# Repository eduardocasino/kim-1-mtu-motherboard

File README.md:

# KIM-1 Motherboard for MTU Cards

## **WARNING**

**ALTHOUGH THE CARDS HAVE BEEN TESTED NOW, THERE MAY BE MORE ERRORS. USE AT YOUR OWN RISK!!!**

If you ordered the first revision PCB, please see the "Rev. 1 Fix" section below.

If you ordered earlier revisions of the aux cards (RS-232 and USB), please see the "Aux. Cards Fix" section below. 

## **UPDATE**

There is now a third auxiliary card option, for connecting the KIM-1 terminal wirelessly using an ESP8266. This new board is not affected by the problems referred above.

This card requires to transfer its firmware to the ESP8266. [Please, see the set up instructions here](https://github.com/eduardocasino/kim-1-mtu-motherboard/blob/main/kim-1-aux-card-esp/README.md)

## About

Welcome to my KIM-1 Motherboardfor MTU cards repository.

This board follows the MTU standard for the KIM-1 expansion and application buses and enables to connect up to five cards, like the [K-1008](https://github.com/eduardocasino/k-1008-visable-memory-card-replica). All the CPU lines are buffered. Additionally, all signals of the KIM-1 ports are replicated on corresponding edge connectors to allow further expansions.

Two audio jacks allow for cassette deck connection and two optional daughterboards provide IEC and RS-232 or USB serial connections, and also a connector compatible with Corsham's SD Shield.

The MTU bus connects 1 to 1 to the KIM-1 expansion connector with the exception of pins 2,3, 16, 17, 18, 19, 20 and X, because MTU boards use some of these pins for power and expanded 18 bit address bus (See page 33 of the [MTU Fall 1980 6502 Peripherals and Software catalog](hhttp://retro.hansotten.nl/6502-sbc/mtu/) Lines 19 and 20 are connected to pins J (K7) and K (DECODE ENABLE) of the KIM-1 application connector, respectively. Those two signals can be limited to just the first or the first and second connectors by opening some jumpers.

A five screw terminal block provides power connections for both the KIM-1 (GND, +5V and +12V regulated) and the expansion boards (+7.5V and +16V unregulated). 

Detail of the two auxiliary boards:

This is how an example setup with one K-1008 board and a [RAM/ROM expansion card](https://github.com/eduardocasino/kim-1-mtu-ram-rom) would look like:

**NOTE**: [This expansion board is a much simpler option](https://github.com/eduardocasino/kim-1-mtu-expansion-card) if you just need to connect some MTU cards. Those are engineered so they put less than 1 TTL load on the CPU buses, so no buffering is really needed. Why the buffering, then? Well, just for fun.

## Licensing

This is a personal project that I am sharing in case it is of interest to any retrocomputing enthusiast and all the information in this repository is provided "as is", without warranty of any kind. I am not liable for any damages that may occur, whether it be to individuals, objects, KIM-1 computers, kittens or any other pets.

This work is licensed under a [Creative Commons Attribution-ShareAlike 4.0 International License](http://creativecommons.org/licenses/by-sa/4.0/).

See the LICENSE.md file for details.

## Rev. 1 Fix

If you tried to build revision 1 of this board, you found out that it does not work (See [Issue #2](https://github.com/eduardocasino/kim-1-mtu-motherboard/issues/2))

You can [install this simple PCB](https://github.com/eduardocasino/kim-1-mtu-motherboard/rev-1-fix) or, alternatively, perform this bodge on the back of the PCB:

Using a cutter, carefully cut these two spokes at pin 19 of U4:

Grab a 14 pin IC socket with flat pins. Bend pins 1,2,3,7 and 14 outwards and cut the rest.

Solder wires to the pins as per this image:

Cover the back of the socket with non conductive tape. Attach the wires to these spots on the motherboard:

Place a 74LS00 in the socket (check the orientation!) and fix evrything to the PCB using some tape, like in this image. I took K7 from another pin, but it is all the same:

## Aux. Cards Fix

If you tried to build earlier revisions of the auxiliary boards (both RS-232 and USB), you may have found out that they do not work with Corsham's SD Shield, although they work fine with IEC disks (See [Issue #3](https://github.com/eduardocasino/kim-1-mtu-motherboard/issues/3))

If you need them to work with the SD Shield, you can perform this simple fix. **WARNING: Doing so, the cards will no longer work with IEC disks**

The fix is the same for both cards. Using a cutter, carefully cut these two tracks:

## Changelog
#### 17/02/2024
* Release Rev. 3 (fixes the auxiliary cards, the motherboard is unchanged)
* IEC socket footprint also supports Commodore-style sockets
* Add instructions to fix original auxiliary boards so they work with IEC disks.

#### 21/01/2024
* Release Rev. 2
* Add instructions to fix Rev. 1 boards.

#### 03/01/2024
* Minor silkscreen update

#### 02/01/2024
* Disable data bus transceiver when DECEN or K7 are active (low)

## Acknowledgements

* Hans Otten and his [Retro Computing blog](http://retro.hansotten.nl/). Documentation of MTU's line of hardware expansions for the KIM-1

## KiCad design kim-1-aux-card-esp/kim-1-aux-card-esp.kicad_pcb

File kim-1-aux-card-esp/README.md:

## Wireless terminal board

This design is based on a setup by Ryan Roth, mentioned in this [Google Groups thread](https://groups.google.com/g/pal6502/c/w8N0uSgJXQY), and the ESP8266 needs to be [programmed with his firmware](https://github.com/ryaneroth/ESP8266-SerialTelnet). For convenience, I keep a [copy of his repo here](https://github.com/eduardocasino/ESP8266-SerialTelnet).

## Firmware install instructions

1. Download and install the latest **Arduino IDE 2.X (preferred) or 1.6.X** from [https://www.arduino.cc/en/Main/Software](https://www.arduino.cc/en/Main/Software)

2. Install **ESP8266** Arduino support using Boards Manager: [https://github.com/esp8266/Arduino#installing-with-boards-manager](https://github.com/esp8266/Arduino#installing-with-boards-manager)

    ***Only*** for IDE 1.6.X, force install version >= 2.4.0. Replace package URL with: [https://github.com/esp8266/Arduino/releases/download/2.4.0-rc1/package_esp8266com_index.json](https://github.com/esp8266/Arduino/releases/download/2.4.0-rc1/package_esp8266com_index.json)

3. Install Install the following libraries:
    * WifiManager: [https://github.com/tzapu/WiFiManager#install-through-library-manager](https://github.com/tzapu/WiFiManager#install-through-library-manager)

4. Put the three bridges in the "**FLASH**" position and connect the board to your computer using an USB to serial adapter.

5. Select board `Generic ESP8266Module`

6. Upload the Sketch contained in `telnetserver` folder from the [ESP8266-SerialTelnet](https://github.com/eduardocasino/ESP8266-SerialTelnet) repo.

7. The moment the `Connecting...` message appears in the console, press the "**RESET**" button and, while holding it", press momentarily the "**FLASH**" button. Then, release the "**RESET**" button. Wait until the sketch is uploaded.

8. Connect to the ESP8266 WiFi network and go to "http://192.168.4.1". Configure connection to your AP, set password, then switch back to your local wifi

9. Disconnect the card and put the bridges back to the "**RUN**" position. Now, you can install it into the motherboard.

10. Connect to the ESP8266 using a Telnet client. Set local echo to off.

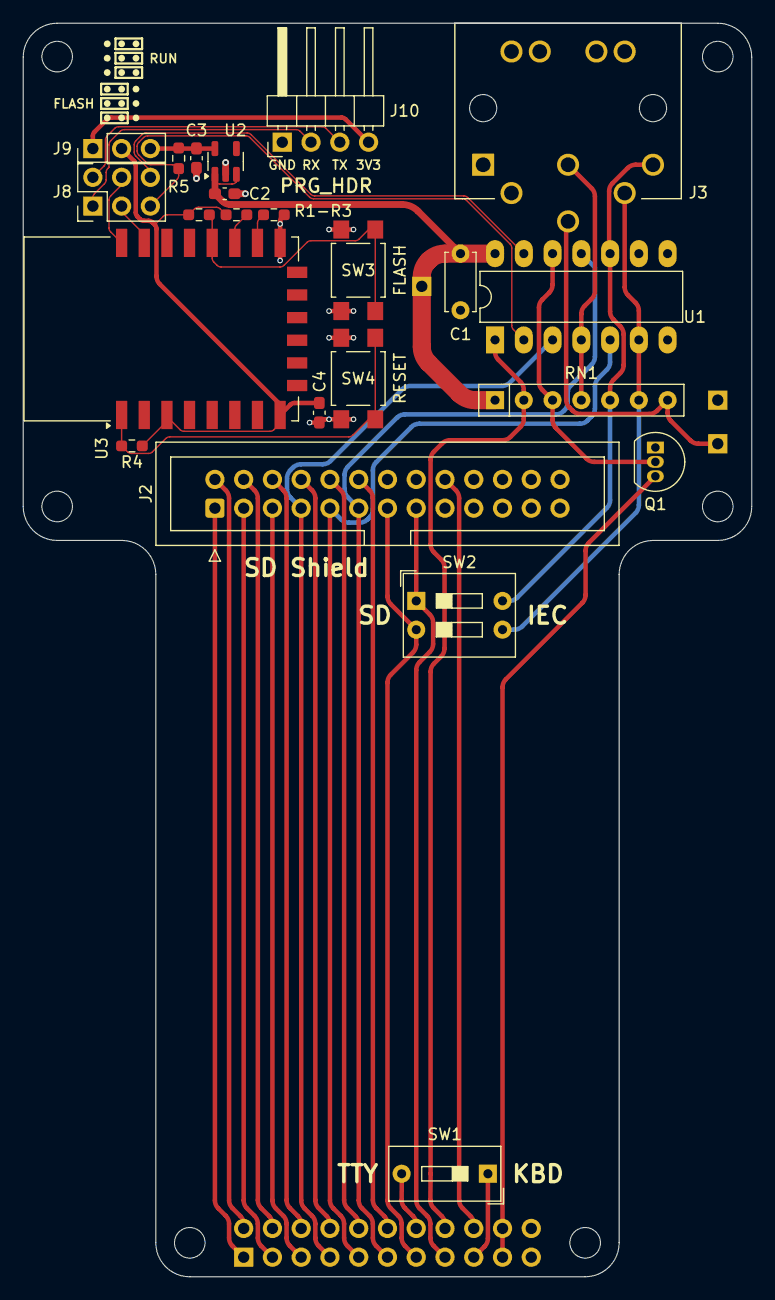
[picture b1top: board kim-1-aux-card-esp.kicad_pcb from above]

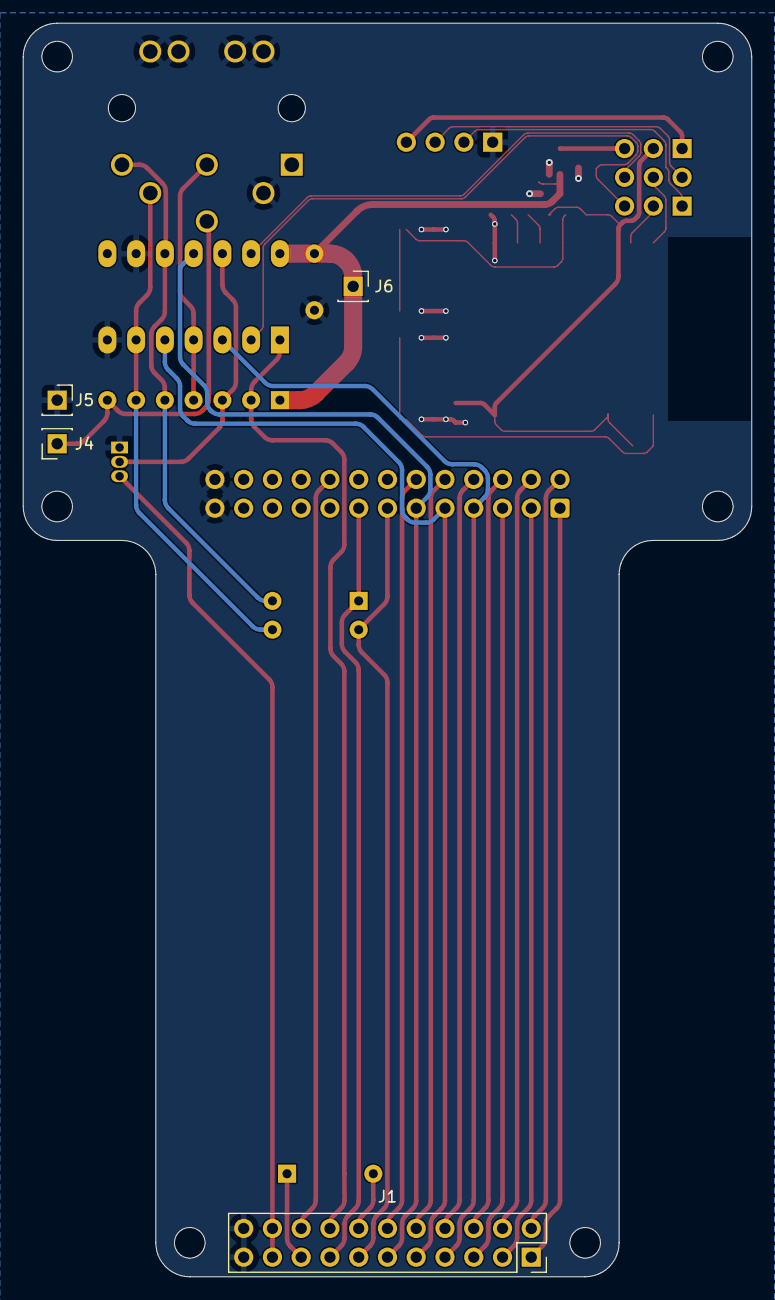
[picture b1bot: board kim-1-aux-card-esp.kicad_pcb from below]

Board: 2 copper layers, 64.3 x 110.7 mm, 27 parts (4 on the bottom side), 39 nets.

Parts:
C1: 100nF; C_Disc_D5.0mm_W2.5mm_P5.00mm
C2, C3: 1uF; C_0603_1608Metric_Pad1.08x0.95mm_HandSolder
C4: 100nF; C_0603_1608Metric_Pad1.08x0.95mm_HandSolder
J1: Motherboard; PinSocket_2x11_P2.54mm_Vertical
J2: SD_Shield; IDC-Header_2x13_P2.54mm_Vertical
J3: DIN-6; CUI_SDS-60J
J4: Reset; PinSocket_1x01_P2.54mm_Vertical
J5: GND; PinSocket_1x01_P2.54mm_Vertical
J6: +5V; PinSocket_1x01_P2.54mm_Vertical
J8: RUN_FLASH; PinHeader_2x03_P2.54mm_Vertical
J9: RUN_FLASH; PinHeader_1x03_P2.54mm_Vertical
J10: PRG_HDR; PinHeader_1x04_P2.54mm_Horizontal
Q1: PN2222A; TO-92_Inline
R1, R2, R3, R4, R5: 10K; R_0603_1608Metric_Pad0.98x0.95mm_HandSolder
RN1: 3K3; R_Array_SIP7
SW1: TTY_KBD; SW_DIP_SPSTx01_Slide_9.78x4.72mm_W7.62mm_P2.54mm
SW2: SD_IEC; SW_DIP_SPSTx02_Slide_9.78x7.26mm_W7.62mm_P2.54mm
SW3: FLASH; SW_SPST_TL3305A
SW4: RESET; SW_SPST_TL3305A
U1: 74LS06; DIP-14_W7.62mm_LongPads
U2: TPS7A0233DBVR; SOT-23-5
U3: ESP-12F; ESP-12E

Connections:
+3V3: C3.1, J9.3, R5.1, U2.5 (OUT)
+5V: C1.1, C2.1, J6.1, RN1.1 (R1), U1.14 (VCC), U2.1 (IN), U2.3 (EN)
/COLA: J1.14, SW1.2
/KBD: J1.19, J1.20, Q1.3 (C)
/PA0: J1.1, J2.1
/PA1: J1.3, J2.3
/PA2: J1.5, J2.5
/PA3: J1.7, J2.7, U1.3
/PA4: J1.9, J2.9, U1.5
/PA5: J1.11, J2.11, U1.11
/PA6: J1.13, J2.13, SW2.2
/PA7: J1.15, J2.15, SW2.1
/PB0: J1.2, J2.2
/PB1: J1.4, J2.4
/PB2: J1.6, J2.6
/PB3: J1.8, J2.8
/PB4: J1.10, J2.10
/PB5: J1.12, J2.12
/PB7: J1.18, J2.18
/PTR: J1.16, RN1.2 (R1.2), U1.1
/ROW3: J1.17, SW1.1
GND: C1.2, C2.2, C3.2, C4.1, J1.21, J1.22, J2.25, J2.26, J3.2, J3.E1, J3.E2, J5.1, J10.1, Q1.1 (E), R3.2, SW3.1 (A), SW4.1 (A), U1.7 (GND), U1.9, U2.2 (GND), U3.15 (GND)
unnamed: J3.6, J4.1, RN1.7 (R6.2)
unnamed: J8.3, U3.21 (GPIO3/RXD)
unnamed: J8.4, U3.22 (GPIO1/TXD)
unnamed: J8.5, R5.2, U1.2
unnamed: J8.6, U1.13
unnamed: C4.2, J9.2, R1.1, R2.1, R4.1, U3.3 (EN), U3.8 (VCC)
unnamed: J8.1, J10.2
unnamed: J8.2, J10.3
unnamed: J9.1, J10.4
unnamed: Q1.2 (B), RN1.3 (R2.2), U1.12
unnamed: J3.3, RN1.4 (R3.2), U1.4
unnamed: J3.5, RN1.5 (R4.2), SW2.4, U1.10
unnamed: J3.4, RN1.6 (R5.2), SW2.3, U1.6
unnamed: R1.2, SW3.2 (B), U3.18 (GPIO0)
unnamed: R4.2, SW4.2 (B), U3.1 (~RST)
unnamed: R2.2, U3.17 (GPIO2)
unnamed: R3.1, U3.16 (GPIO15)

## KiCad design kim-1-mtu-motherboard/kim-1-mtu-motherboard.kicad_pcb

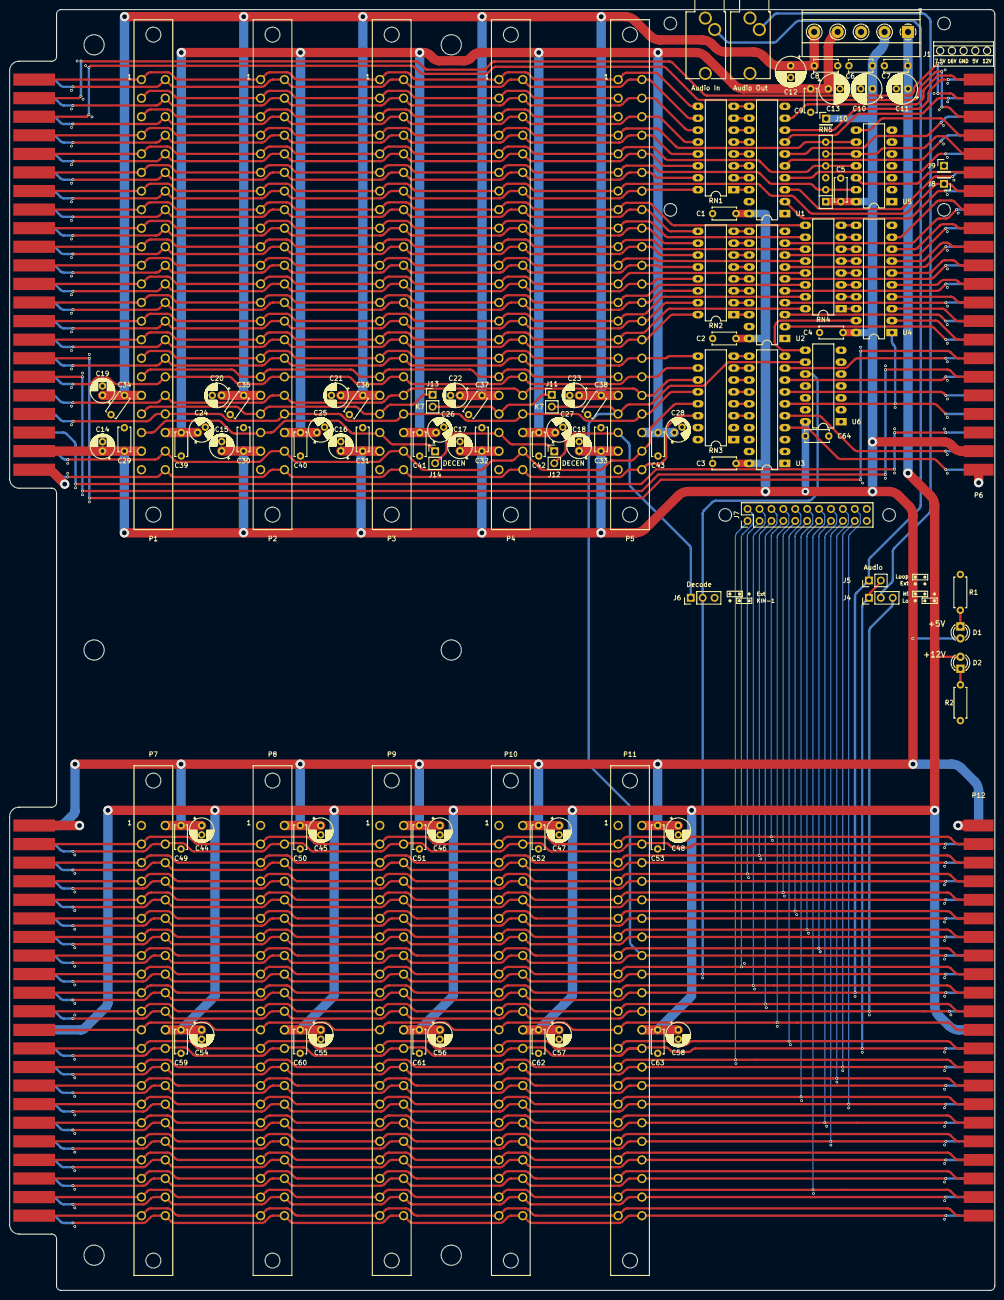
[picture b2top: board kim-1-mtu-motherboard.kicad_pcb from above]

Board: 2 copper layers, 210.0 x 273.0 mm, 107 parts (0 on the bottom side), 161 nets.

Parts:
C1, C2, C3, C4, C5, C6, C7, C8, C9, C29, C30, C31, C32, C33, C34, C35, C36, C37, C38, C39, C40, C41, C42, C43, C49, C50, C51, C52, C53, C59, C60, C61, C62, C63, C64: 100nF; C_Disc_D5.0mm_W2.5mm_P5.00mm
C10, C11, C12, C13: 100uF; CP_Radial_D6.3mm_P2.50mm
C14, C15, C16, C17, C18, C19, C20, C21, C22, C23, C24, C25, C26, C27, C28, C44, C45, C46, C47, C48, C54, C55, C56, C57, C58: 47uF; CP_Radial_D5.0mm_P2.00mm
D1: RED; LED_D3.0mm
D2: YELLOW; LED_D3.0mm
J1: Power_Connector; TerminalBlock_Phoenix_MKDS-1,5-5_1x05_P5.00mm_Horizontal
J2: Audio Out; Jack_3.5mm_35RAPC2AVN4_Horizontal_CircularHoles
J3: Audio In; Jack_3.5mm_35RAPC2AVN4_Horizontal_CircularHoles
J4: Audio HI/LO; PinHeader_1x03_P2.54mm_Vertical
J5: Audio Loop; PinHeader_1x02_P2.54mm_Vertical
J6: Decode; PinHeader_1x03_P2.54mm_Vertical
J7: Daughterboard; PinHeader_2x11_P2.54mm_Vertical
J8: RESET; PinHeader_1x01_P2.54mm_Vertical
J9, J10: GND; PinHeader_1x01_P2.54mm_Vertical
J11, J13: K7; PinHeader_1x02_P2.54mm_Vertical
J12, J14: DECEN; PinHeader_1x02_P2.54mm_Vertical
P1, P2, P3, P4, P5, P7, P8, P9, P10, P11: EXP_BOARD; EDAC-3.96-2x22
P6, P12: KIM-1; KIM_EDGE
P13: KIM_EXP; KIM_CONN
P14: KIM_APPL; KIM_CONN
R1: 330R; R_Axial_DIN0207_L6.3mm_D2.5mm_P7.62mm_Horizontal
R2: 1K; R_Axial_DIN0207_L6.3mm_D2.5mm_P7.62mm_Horizontal
RN1, RN2, RN3, RN4: 33R; DIP-16_W7.62mm_LongPads
RN5: 3K3; R_Array_SIP6
U1, U2, U3: 74HCT541; DIP-20_W7.62mm_LongPads
U4: 74LS245; DIP-20_W7.62mm_LongPads
U5: 74LS07; DIP-14_W7.62mm_LongPads
U6: 74LS00; DIP-14_W7.62mm_LongPads

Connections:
+5V: C1.1, C2.1, C3.1, C4.1, C5.1, C6.2, C10.1, C14.1, C15.1, C16.1, C17.1, C18.1, C29.1, C30.1, C31.1, C32.1, C33.1, C44.1, C45.1, C46.1, C47.1, C48.1, C49.1, C50.1, C51.1, C52.1, C53.1, C64.1, D1.2 (A), J1.2, J10.1, P1.21 (+5V), P2.21 (+5V), P3.21 (+5V), P4.21 (+5V), P5.21 (+5V), P6.21 (+5V), P7.A (+5V), P8.A (+5V), P9.A (+5V), P10.A (+5V), P11.A (+5V), P12.A (+5V), P13.21 (+5V), P14.A (+5V), RN5.1 (common), U1.20 (VCC), U2.20 (VCC), U3.20 (VCC), U4.20 (VCC), U5.14 (VCC), U6.14 (VCC)
+7.5V_RAW: C8.2, C12.1, C19.1, C20.1, C21.1, C22.1, C23.1, C34.1, C35.1, C36.1, C37.1, C38.1, J1.5, P1.18 (+7.5V_RAW), P2.18 (+7.5V_RAW), P3.18 (+7.5V_RAW), P4.18 (+7.5V_RAW), P5.18 (+7.5V_RAW)
+12V: C7.2, C11.1, C54.1, C55.1, C56.1, C57.1, C58.1, C59.1, C60.1, C61.1, C62.1, C63.1, D2.2 (A), J1.1, P7.N (+12V), P8.N (+12V), P9.N (+12V), P10.N (+12V), P11.N (+12V), P12.N (+12V), P14.N (+12V)
+16V_RAW: C9.2, C13.1, C24.1, C25.1, C26.1, C27.1, C28.1, C39.1, C40.1, C41.1, C42.1, C43.1, J1.4, P1.X (+16V_RAW), P2.X (+16V_RAW), P3.X (+16V_RAW), P4.X (+16V_RAW), P5.X (+16V_RAW)
/A0: P6.A (A0), U1.8 (A6)
/A1: P6.B (A1), U1.7 (A5)
/A2: P6.C (A2), U1.6 (A4)
/A3: P6.D (A3), U1.5 (A3)
/A4: P6.E (A4), U1.4 (A2)
/A5: P6.F (A5), U1.3 (A1)
/A6: P6.H (A6), U1.2 (A0)
/A7: P6.J (A7), U2.9 (A7)
/A8: P6.K (A8), U2.8 (A6)
/A9: P6.L (A9), U2.7 (A5)
/A10: P6.M (A10), U2.6 (A4)
/A11: P6.N (A11), U2.5 (A3)
/A12: P6.P (A12), U2.4 (A2)
/A13: P6.R (A13), U2.3 (A1)
/A14: P6.S (A14), U2.2 (A0)
/A15: P6.T (A15), U3.9 (A7)
/AUDIN: J3.T, J5.1, P7.L (AUDIN), P8.L (AUDIN), P9.L (AUDIN), P10.L (AUDIN), P11.L (AUDIN), P12.L (AUDIN), P14.L (AUDIN)
/AUD_H: J4.1, J5.2, P7.P (AUD_H), P8.P (AUD_H), P9.P (AUD_H), P10.P (AUD_H), P11.P (AUD_H), P12.P (AUD_H), P14.P (AUD_H)
/AUD_L: J4.3, P7.M (AUD_L), P8.M (AUD_L), P9.M (AUD_L), P10.M (AUD_L), P11.M (AUD_L), P12.M (AUD_L), P14.M (AUD_L)
/BA0: P1.A (A0), P2.A (A0), P3.A (A0), P4.A (A0), P5.A (A0), P13.A (A0), RN1.10 (R7.2)
/BA1: P1.B (A1), P2.B (A1), P3.B (A1), P4.B (A1), P5.B (A1), P13.B (A1), RN1.11 (R6.2)
/BA2: P1.C (A2), P2.C (A2), P3.C (A2), P4.C (A2), P5.C (A2), P13.C (A2), RN1.12 (R5.2)
/BA3: P1.D (A3), P2.D (A3), P3.D (A3), P4.D (A3), P5.D (A3), P13.D (A3), RN1.13 (R4.2)
/BA4: P1.E (A4), P2.E (A4), P3.E (A4), P4.E (A4), P5.E (A4), P13.E (A4), RN1.14 (R3.2)
/BA5: P1.F (A5), P2.F (A5), P3.F (A5), P4.F (A5), P5.F (A5), P13.F (A5), RN1.15 (R2.2)
/BA6: P1.H (A6), P2.H (A6), P3.H (A6), P4.H (A6), P5.H (A6), P13.H (A6), RN1.16 (R1.2)
/BA7: P1.J (A7), P2.J (A7), P3.J (A7), P4.J (A7), P5.J (A7), P13.J (A7), RN2.9 (R8.2)
/BA8: P1.K (A8), P2.K (A8), P3.K (A8), P4.K (A8), P5.K (A8), P13.K (A8), RN2.10 (R7.2)
/BA9: P1.L (A9), P2.L (A9), P3.L (A9), P4.L (A9), P5.L (A9), P13.L (A9), RN2.11 (R6.2)
/BA10: P1.M (A10), P2.M (A10), P3.M (A10), P4.M (A10), P5.M (A10), P13.M (A10), RN2.12 (R5.2)
/BA11: P1.N (A11), P2.N (A11), P3.N (A11), P4.N (A11), P5.N (A11), P13.N (A11), RN2.13 (R4.2)
/BA12: P1.P (A12), P2.P (A12), P3.P (A12), P4.P (A12), P5.P (A12), P13.P (A12), RN2.14 (R3.2)
/BA13: P1.R (A13), P2.R (A13), P3.R (A13), P4.R (A13), P5.R (A13), P13.R (A13), RN2.15 (R2.2)
/BA14: P1.S (A14), P2.S (A14), P3.S (A14), P4.S (A14), P5.S (A14), P13.S (A14), RN2.16 (R1.2)
/BA15: P1.T (A15), P2.T (A15), P3.T (A15), P4.T (A15), P5.T (A15), P13.T (A15), RN3.9 (R8.2)
/BD0: P1.15 (D0), P2.15 (D0), P3.15 (D0), P4.15 (D0), P5.15 (D0), P13.15 (D0), RN4.16 (R1.2)
/BD1: P1.14 (D1), P2.14 (D1), P3.14 (D1), P4.14 (D1), P5.14 (D1), P13.14 (D1), RN4.15 (R2.2)
/BD2: P1.13 (D2), P2.13 (D2), P3.13 (D2), P4.13 (D2), P5.13 (D2), P13.13 (D2), RN4.14 (R3.2)
/BD3: P1.12 (D3), P2.12 (D3), P3.12 (D3), P4.12 (D3), P5.12 (D3), P13.12 (D3), RN4.13 (R4.2)
/BD4: P1.11 (D4), P2.11 (D4), P3.11 (D4), P4.11 (D4), P5.11 (D4), P13.11 (D4), RN4.12 (R5.2)
/BD5: P1.10 (D5), P2.10 (D5), P3.10 (D5), P4.10 (D5), P5.10 (D5), P13.10 (D5), RN4.11 (R6.2)
/BD6: P1.9 (D6), P2.9 (D6), P3.9 (D6), P4.9 (D6), P5.9 (D6), P13.9 (D6), RN4.10 (R7.2)
/BD7: P1.8 (D7), P2.8 (D7), P3.8 (D7), P4.8 (D7), P5.8 (D7), P13.8 (D7), RN4.9 (R8.2)
/BDECEN: J14.1, P1.20 (~DECODE_ENABLE), P2.20 (~DECODE_ENABLE), P3.20 (~DECODE_ENABLE)
/BK7: J13.1, P1.19 (~VECTOR_FETCH), P2.19 (~VECTOR_FETCH), P3.19 (~VECTOR_FETCH)
/BRAMRW: P1.Z (RAMRW), P2.Z (RAMRW), P3.Z (RAMRW), P4.Z (RAMRW), P5.Z (RAMRW), P13.Z (RAMRW), RN3.14 (R3.2)
/BRO: P1.5 (R0), P2.5 (R0), P3.5 (R0), P4.5 (R0), P5.5 (R0), P13.5 (R0), RN5.4 (R3), U5.11
/BR/~W: P1.V (R/~W), P2.V (R/~W), P3.V (R/~W), P4.V (R/~W), P5.V (R/~W), P13.V (R/~W), RN3.11 (R6.2)
/BSYNC: P1.1 (SYNC), P2.1 (SYNC), P3.1 (SYNC), P4.1 (SYNC), P5.1 (SYNC), P13.1 (SYNC), RN1.9 (R8.2)
/B~R/W: P1.W (~R/W), P2.W (~R/W), P3.W (~R/W), P4.W (~R/W), P5.W (~R/W), P13.W (~R/W), RN3.12 (R5.2)
/B~Ø2: P1.Y (~Ø2), P2.Y (~Ø2), P3.Y (~Ø2), P4.Y (~Ø2), P5.Y (~Ø2), P13.Y (~Ø2), RN3.13 (R4.2)
/BØ2: P1.U (Ø2), P2.U (Ø2), P3.U (Ø2), P4.U (Ø2), P5.U (Ø2), P13.U (Ø2), RN3.10 (R7.2)
/COLA: J7.14, P7.21 (COLA), P8.21 (COLA), P9.21 (COLA), P10.21 (COLA), P11.21 (COLA), P12.21 (COLA), P14.21 (COLA)
/COLB: P7.19 (COLB), P8.19 (COLB), P9.19 (COLB), P10.19 (COLB), P11.19 (COLB), P12.19 (COLB), P14.19 (COLB)
/COLC: P7.Y (COLC), P8.Y (COLC), P9.Y (COLC), P10.Y (COLC), P11.Y (COLC), P12.Y (COLC), P14.Y (COLC)
/COLD: P7.22 (COLD), P8.22 (COLD), P9.22 (COLD), P10.22 (COLD), P11.22 (COLD), P12.22 (COLD), P14.22 (COLD)
/COLE: P7.20 (COLE), P8.20 (COLE), P9.20 (COLE), P10.20 (COLE), P11.20 (COLE), P12.20 (COLE), P14.20 (COLE)
/COLF: P7.18 (COLF), P8.18 (COLF), P9.18 (COLF), P10.18 (COLF), P11.18 (COLF), P12.18 (COLF), P14.18 (COLF)
/COLG: P7.W (COLG), P8.W (COLG), P9.W (COLG), P10.W (COLG), P11.W (COLG), P12.W (COLG), P14.W (COLG)
/D0: P6.15 (D0), U4.2 (A0)
/D1: P6.14 (D1), U4.3 (A1)
/D2: P6.13 (D2), U4.4 (A2)
/D3: P6.12 (D3), U4.5 (A3)
/D4: P6.11 (D4), U4.6 (A4)
/D5: P6.10 (D5), U4.7 (A5)
/D6: P6.9 (D6), U4.8 (A6)
/D7: P6.8 (D7), U4.9 (A7)
/DECEN: J6.2, P7.K (DECEN), P8.K (DECEN), P9.K (DECEN), P10.K (DECEN), P11.K (DECEN), P12.K (DECEN), P14.K (DECEN), U6.10
/K0: P7.B (K0), P8.B (K0), P9.B (K0), P10.B (K0), P11.B (K0), P12.B (K0), P14.B (K0)
/K1: P7.C (K1), P8.C (K1), P9.C (K1), P10.C (K1), P11.C (K1), P12.C (K1), P14.C (K1)
/K2: P7.D (K2), P8.D (K2), P9.D (K2), P10.D (K2), P11.D (K2), P12.D (K2), P14.D (K2)
/K3: P7.E (K3), P8.E (K3), P9.E (K3), P10.E (K3), P11.E (K3), P12.E (K3), P14.E (K3)
/K4: P7.F (K4), P8.F (K4), P9.F (K4), P10.F (K4), P11.F (K4), P12.F (K4), P14.F (K4)
/K5: P7.H (K5), P8.H (K5), P9.H (K5), P10.H (K5), P11.H (K5), P12.H (K5), P14.H (K5)
/K6: P6.16 (K6), P13.16 (K6)
/K7: J11.2, P5.19 (~VECTOR_FETCH), P7.J (K7), P8.J (K7), P9.J (K7), P10.J (K7), P11.J (K7), P12.J (K7), P14.J (K7), U6.9
/KBD: J7.20, P7.T (KBD), P8.T (KBD), P9.T (KBD), P10.T (KBD), P11.T (KBD), P12.T (KBD), P14.T (KBD)
/KBD_R: J7.19, P7.R (KBD_R), P8.R (KBD_R), P9.R (KBD_R), P10.R (KBD_R), P11.R (KBD_R), P12.R (KBD_R), P14.R (KBD_R)
/PA0: J7.1, P7.14 (PA0), P8.14 (PA0), P9.14 (PA0), P10.14 (PA0), P11.14 (PA0), P12.14 (PA0), P14.14 (PA0)
/PA1: J7.3, P7.4 (PA1), P8.4 (PA1), P9.4 (PA1), P10.4 (PA1), P11.4 (PA1), P12.4 (PA1), P14.4 (PA1)
/PA2: J7.5, P7.3 (PA2), P8.3 (PA2), P9.3 (PA2), P10.3 (PA2), P11.3 (PA2), P12.3 (PA2), P14.3 (PA2)
/PA3: J7.7, P7.2 (PA3), P8.2 (PA3), P9.2 (PA3), P10.2 (PA3), P11.2 (PA3), P12.2 (PA3), P14.2 (PA3)
/PA4: J7.9, P7.5 (PA4), P8.5 (PA4), P9.5 (PA4), P10.5 (PA4), P11.5 (PA4), P12.5 (PA4), P14.5 (PA4)
/PA5: J7.11, P7.6 (PA5), P8.6 (PA5), P9.6 (PA5), P10.6 (PA5), P11.6 (PA5), P12.6 (PA5), P14.6 (PA5)
/PA6: J7.13, P7.7 (PA6), P8.7 (PA6), P9.7 (PA6), P10.7 (PA6), P11.7 (PA6), P12.7 (PA6), P14.7 (PA6)
/PA7: J7.15, P7.8 (PA7), P8.8 (PA7), P9.8 (PA7), P10.8 (PA7), P11.8 (PA7), P12.8 (PA7), P14.8 (PA7)
/PB0: J7.2, P7.9 (PB0), P8.9 (PB0), P9.9 (PB0), P10.9 (PB0), P11.9 (PB0), P12.9 (PB0), P14.9 (PB0)
/PB1: J7.4, P7.10 (PB1), P8.10 (PB1), P9.10 (PB1), P10.10 (PB1), P11.10 (PB1), P12.10 (PB1), P14.10 (PB1)
/PB2: J7.6, P7.11 (PB2), P8.11 (PB2), P9.11 (PB2), P10.11 (PB2), P11.11 (PB2), P12.11 (PB2), P14.11 (PB2)
/PB3: J7.8, P7.12 (PB3), P8.12 (PB3), P9.12 (PB3), P10.12 (PB3), P11.12 (PB3), P12.12 (PB3), P14.12 (PB3)
/PB4: J7.10, P7.13 (PB4), P8.13 (PB4), P9.13 (PB4), P10.13 (PB4), P11.13 (PB4), P12.13 (PB4), P14.13 (PB4)
/PB5: J7.12, P7.16 (PB5), P8.16 (PB5), P9.16 (PB5), P10.16 (PB5), P11.16 (PB5), P12.16 (PB5), P14.16 (PB5)
/PB7: J7.18, P7.15 (PB7), P8.15 (PB7), P9.15 (PB7), P10.15 (PB7), P11.15 (PB7), P12.15 (PB7), P14.15 (PB7)
/PIN_2: P1.2 (PIN_2), P2.2 (PIN_2), P3.2 (PIN_2), P4.2 (PIN_2), P5.2 (PIN_2)
/PIN_3: P1.3 (PIN_3), P2.3 (PIN_3), P3.3 (PIN_3), P4.3 (PIN_3), P5.3 (PIN_3)
/PIN_16: P1.16 (PIN_16), P2.16 (PIN_16), P3.16 (PIN_16), P4.16 (PIN_16), P5.16 (PIN_16)
/PIN_17: P1.17 (PIN_17), P2.17 (PIN_17), P3.17 (PIN_17), P4.17 (PIN_17), P5.17 (PIN_17)
/PLL: P6.X (PLL), P13.X (PLL)
/PTR: J7.16, P7.U (PTR), P8.U (PTR), P9.U (PTR), P10.U (PTR), P11.U (PTR), P12.U (PTR), P14.U (PTR)
/PTR_R: P7.S (PTR_R), P8.S (PTR_R), P9.S (PTR_R), P10.S (PTR_R), P11.S (PTR_R), P12.S (PTR_R), P14.S (PTR_R)
/RAMRW: P6.Z (RAMRW), U3.4 (A2)
/RO: P6.5 (R0), RN5.5 (R4), U5.10
/ROW0: P7.17 (ROW0), P8.17 (ROW0), P9.17 (ROW0), P10.17 (ROW0), P11.17 (ROW0), P12.17 (ROW0), P14.17 (ROW0)
/ROW1: P7.Z (ROW1), P8.Z (ROW1), P9.Z (ROW1), P10.Z (ROW1), P11.Z (ROW1), P12.Z (ROW1), P14.Z (ROW1)
/ROW2: P7.X (ROW2), P8.X (ROW2), P9.X (ROW2), P10.X (ROW2), P11.X (ROW2), P12.X (ROW2), P14.X (ROW2)
/ROW3: J7.17, P7.V (ROW3), P8.V (ROW3), P9.V (ROW3), P10.V (ROW3), P11.V (ROW3), P12.V (ROW3), P14.V (ROW3)
/R/~W: P6.V (R/~W), U3.7 (A5)
/SST: P6.17 (SST), P13.17 (SST)
/SYNC: P6.1 (SYNC), U1.9 (A7)
/~BIRQ: P1.4 (~IRQ), P2.4 (~IRQ), P3.4 (~IRQ), P4.4 (~IRQ), P5.4 (~IRQ), P13.4 (~IRQ), RN5.6 (R5), U5.9
/~BNMI: P1.6 (~NMI), P2.6 (~NMI), P3.6 (~NMI), P4.6 (~NMI), P5.6 (~NMI), P13.6 (~NMI), RN5.2 (R1), U5.13
/~IRQ: P6.4 (~IRQ), U5.8
/~NMI: P6.6 (~NMI), U5.12
/~RDY: P6.2 (~RDY), P13.2 (~RDY)
/~RES: J8.1, P1.7 (~RES), P2.7 (~RES), P3.7 (~RES), P4.7 (~RES), P5.7 (~RES), P6.7 (~RES), P13.7 (~RES)
/~R/W: P6.W (~R/W), U3.6 (A4), U4.1 (A->B)
/~Ø2: P6.Y (~Ø2), U3.5 (A3)
/Ø1: P6.3 (Ø1), P13.3 (Ø1)
/Ø2: P6.U (Ø2), U3.8 (A6)
GND: C1.2, C2.2, C3.2, C4.2, C5.2, C6.1, C7.1, C8.1, C9.1, C10.2, C11.2, C12.2, C13.2, C14.2, C15.2, C16.2, C17.2, C18.2, C19.2, C20.2, C21.2, C22.2, C23.2, C24.2, C25.2, C26.2, C27.2, C28.2, C29.2, C30.2, C31.2, C32.2, C33.2, C34.2, C35.2, C36.2, C37.2, C38.2, C39.2, C40.2, C41.2, C42.2, C43.2, C44.2, C45.2, C46.2, C47.2, C48.2, C49.2, C50.2, C51.2, C52.2, C53.2, C54.2, C55.2, C56.2, C57.2, C58.2, C59.2, C60.2, C61.2, C62.2, C63.2, C64.2, J1.3, J2.S, J3.S, J6.3, J7.21, J7.22, J9.1, P1.22 (GND), P2.22 (GND), P3.22 (GND), P4.22 (GND), P5.22 (GND), P6.22 (GND), P7.1 (GND), P8.1 (GND), P9.1 (GND), P10.1 (GND), P11.1 (GND), P12.1 (GND), P13.22 (GND), P14.1 (GND), R1.1, R2.2, U1.1 (G1), U1.10 (GND), U1.19 (G2), U2.1 (G1), U2.10 (GND), U2.19 (G2), U3.1 (G1), U3.2 (A0), U3.3 (A1), U3.10 (GND), U3.19 (G2), U4.10 (GND), U5.1, U5.3, U5.5, U5.7 (GND), U6.1, U6.2, U6.4, U6.5, U6.7 (GND), U6.12, U6.13
unnamed: D1.1 (K), R1.2
unnamed: D2.1 (K), R2.1
unnamed: J2.T, J4.2
unnamed: J11.1, J13.2, P4.19 (~VECTOR_FETCH)
unnamed: J12.1, J14.2, P4.20 (~DECODE_ENABLE)
unnamed: J6.1, J12.2, P5.20 (~DECODE_ENABLE)
unnamed: RN1.1 (R1.1), U1.18 (Y0)
unnamed: RN1.2 (R2.1), U1.17 (Y1)
unnamed: RN1.3 (R3.1), U1.16 (Y2)
unnamed: RN1.4 (R4.1), U1.15 (Y3)
unnamed: RN1.5 (R5.1), U1.14 (Y4)
unnamed: RN1.6 (R6.1), U1.13 (Y5)
unnamed: RN1.7 (R7.1), U1.12 (Y6)
unnamed: RN1.8 (R8.1), U1.11 (Y7)
unnamed: RN2.1 (R1.1), U2.18 (Y0)
unnamed: RN2.2 (R2.1), U2.17 (Y1)
unnamed: RN2.3 (R3.1), U2.16 (Y2)
unnamed: RN2.4 (R4.1), U2.15 (Y3)
unnamed: RN2.5 (R5.1), U2.14 (Y4)
unnamed: RN2.6 (R6.1), U2.13 (Y5)
unnamed: RN2.7 (R7.1), U2.12 (Y6)
unnamed: RN2.8 (R8.1), U2.11 (Y7)
unnamed: RN3.3 (R3.1), U3.16 (Y2)
unnamed: RN3.4 (R4.1), U3.15 (Y3)
unnamed: RN3.5 (R5.1), U3.14 (Y4)
unnamed: RN3.6 (R6.1), U3.13 (Y5)
unnamed: RN3.7 (R7.1), U3.12 (Y6)
unnamed: RN3.8 (R8.1), U3.11 (Y7)
unnamed: RN4.1 (R1.1), U4.18 (B0)
unnamed: RN4.2 (R2.1), U4.17 (B1)
unnamed: RN4.3 (R3.1), U4.16 (B2)
unnamed: RN4.4 (R4.1), U4.15 (B3)
unnamed: RN4.5 (R5.1), U4.14 (B4)
unnamed: RN4.6 (R6.1), U4.13 (B5)
unnamed: RN4.7 (R7.1), U4.12 (B6)
unnamed: RN4.8 (R8.1), U4.11 (B7)
unnamed: U4.19 (CE), U6.8

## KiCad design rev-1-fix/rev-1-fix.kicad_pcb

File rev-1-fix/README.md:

# Fix for KIM-1 Motherboard

## **WARNING**

**ALTHOUGH THIS FIX SEEMS TO BE WORKING SO FAR, IT STILL NEEDS MORE TESTING. USE AT YOUR OWN RISK!!!**

## About

This simple PCB fixes the first revision of the KIM-1 motherboard. Just put it in place of U4 and follow the install instructions.

(See [Issue #2](https://github.com/eduardocasino/kim-1-mtu-motherboard/issues/2))

**NOTE: This is only necessary for the first revision of the motherboard. Rev. 2 is already corrected.**

## Installation

Carefully drill a 2mm hole in this position:

Solder sufficiently long cables to K7 and DECEN pads of the fix board.

Remove C4 and place the fix board in place of U4. Pass the cables through the newly drilled hole.

Solder the cables to the back of the motherboard at these spots:

## Licensing

This is a personal project that I am sharing in case it is of interest to any retrocomputing enthusiast and all the information in this repository is provided "as is", without warranty of any kind. I am not liable for any damages that may occur, whether it be to individuals, objects, KIM-1 computers, kittens or any other pets.

This work is licensed under a [Creative Commons Attribution-ShareAlike 4.0 International License](http://creativecommons.org/licenses/by-sa/4.0/).

See the LICENSE.md file for details.

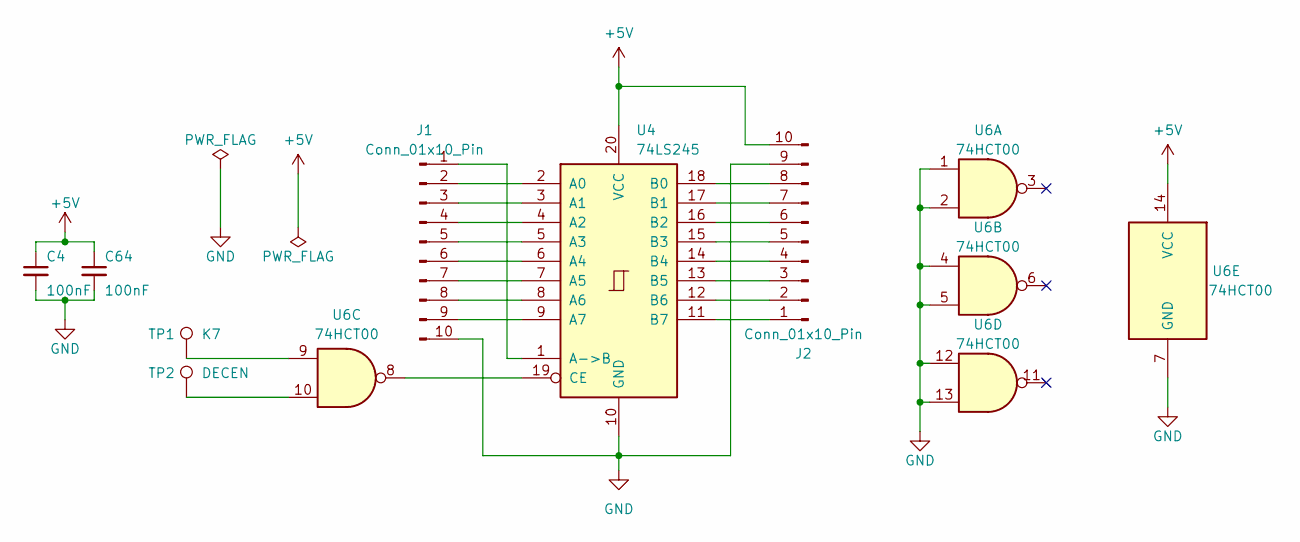
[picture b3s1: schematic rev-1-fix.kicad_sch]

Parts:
C4, C64: 100nF; C_Disc_D5.0mm_W2.5mm_P5.00mm
J1, J2: Conn_01x10_Pin; PinHeader_1x10_P2.54mm_Vertical
TP1: K7; TestPoint_THTPad_D1.5mm_Drill0.7mm
TP2: DECEN; TestPoint_THTPad_D1.5mm_Drill0.7mm
U4: 74LS245; DIP-20_W7.62mm_LongPads
U6: 74HCT00; DIP-14_W7.62mm_LongPads

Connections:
+5V: C4.1, C64.1, J2.10, U4.20 (VCC), U6.14 (VCC)
GND: C4.2, C64.2, J1.10, J2.9, U4.10 (GND), U6.1, U6.2, U6.4, U6.5, U6.7 (GND), U6.12, U6.13
unnamed: J1.1, U4.1 (A->B)
unnamed: J1.2, U4.2 (A0)
unnamed: J1.3, U4.3 (A1)
unnamed: J1.4, U4.4 (A2)
unnamed: J1.5, U4.5 (A3)
unnamed: J1.6, U4.6 (A4)
unnamed: J1.7, U4.7 (A5)
unnamed: J1.8, U4.8 (A6)
unnamed: J1.9, U4.9 (A7)
unnamed: J2.1, U4.11 (B7)
unnamed: J2.2, U4.12 (B6)
unnamed: J2.3, U4.13 (B5)
unnamed: J2.4, U4.14 (B4)
unnamed: J2.5, U4.15 (B3)
unnamed: J2.6, U4.16 (B2)
unnamed: J2.7, U4.17 (B1)
unnamed: J2.8, U4.18 (B0)
unnamed: TP1.1, U6.9
unnamed: TP2.1, U6.10
unnamed: U4.19 (CE), U6.8

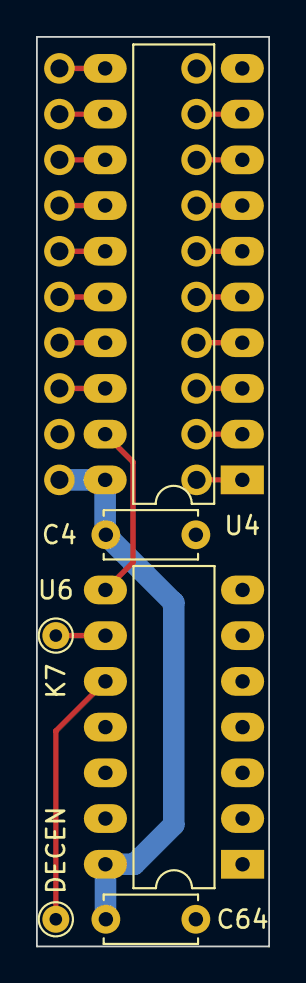
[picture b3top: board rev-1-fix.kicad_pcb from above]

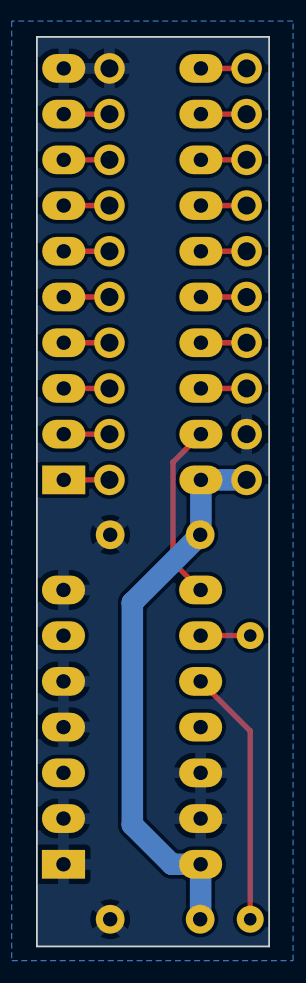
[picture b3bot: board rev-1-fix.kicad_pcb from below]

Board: 2 copper layers, 12.9 x 50.5 mm, 8 parts (2 on the bottom side), 22 nets.

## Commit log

2023-11-19 Fix image URLs
2023-11-19 Fix URL to MTU catalog
2023-11-19 Crop images
2023-12-30 Add warning message
2024-01-02 Disable data bus transceiver when DECEN or K7 active (low). Should fix issue #2
2024-01-21 Add fix for Rev. 1 boards
2024-01-21 Fix image links
2024-01-21 Minor silkscreen fix
2024-01-21 Add fix instructions
2024-01-21 Fix IC number
2024-01-28 Add warning for issue #3
2024-02-17 Support Commodore-style DIN-6 connectors
2024-02-17 Revision 3. Fixes Issue #3
2024-10-03 New auxiliary board for telnet over wifi terminal
2024-10-03 Minor trace optimizations
2024-12-09 Update info on the ESP WiFi card
2024-12-09 Fix link
